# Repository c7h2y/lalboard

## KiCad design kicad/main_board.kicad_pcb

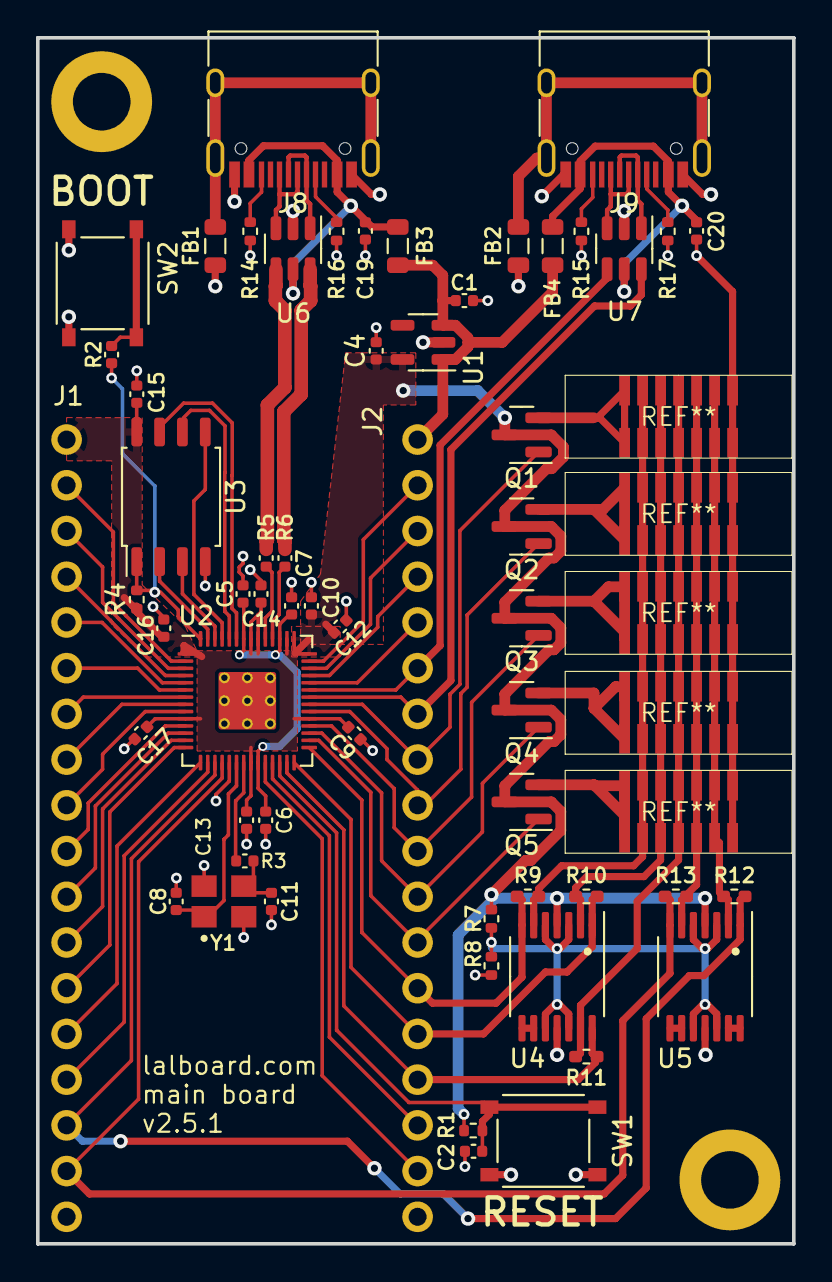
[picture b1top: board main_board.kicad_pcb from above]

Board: 2 copper layers, 42.0 x 67.0 mm, 60 parts (0 on the bottom side), 72 nets.

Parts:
C1: 10u; C_0402_1005Metric
C2, C5, C6, C9, C12, C13, C14, C15, C16, C17, C19, C20: 100n; C_0402_1005Metric
C4: 4.7u; C_0402_1005Metric
C7, C10: 1u; C_0402_1005Metric
C8, C11: 30pF; C_0402_1005Metric
FB1, FB2, FB3, FB4: CBG201209U500T; L_0805_2012Metric
H1, H2: MountingHole_Pad; MountingHole_3.2mm_M3_DIN965_Pad
J1, J2: Conn_01x18; PinHeader_1x18_P2.54mm_Vertical
J8, J9: TYPE-C-31-M-12; USB_C_Receptacle_HRO_TYPE-C-31-M-12
Q1, Q2, Q3, Q4, Q5: DMG2301L-7; SOT-23
R1: 1.5k; R_0402_1005Metric
R2, R3: 1k; C_0402_1005Metric
R4: 10k; R_0402_1005Metric
R5, R6: 27; C_0402_1005Metric
R7: 100k; R_0402_1005Metric
R8: 390k; R_0402_1005Metric
R9, R10, R11, R12, R13: 2k; R_0402_1005Metric_Pad0.72x0.64mm_HandSolder
R14, R15, R16, R17: 5.1k; R_0402_1005Metric
SW1: Reset; SW_TS-1187A-B-A-B
SW2: Boot; SW_TS-1187A-B-A-B
U1: XC6220B331MR; SOT-23-5
U2: RP2040; RP2040-QFN-56
U3: W25Q128JVS; SOIC-8_5.23x5.23mm_P1.27mm
U4, U5: COS724; TSSOP-14_4.4x5mm_P0.65mm
U6, U7: USBLC6-2SC6; SOT-23-6
Y1: Crystal_GND24; OSC_X322516MLB4SI

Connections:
+1V1: C5.1, C6.1, C7.1, U2.23 (DVDD), U2.45 (VREG_VOUT), U2.50 (DVDD)
+3.3V: C4.1, C9.1, C10.1, C12.1, C13.1, C14.1, C15.1, C16.1, C17.1, J1.1, Q1.3 (D), Q2.3 (D), Q3.3 (D), Q4.3 (D), Q5.3 (D), R1.1, R4.1, R7.1, U1.5 (VOUT), U2.1 (IOVDD), U2.10 (IOVDD), U2.22 (IOVDD), U2.33 (IOVDD), U2.42 (IOVDD), U2.43 (ADC_AVDD), U2.44 (VREG_IN), U2.48 (USB_VDD), U2.49 (IOVDD), U3.8 (VCC), U4.4 (V+), U5.4 (V+)
+5V: C1.1, FB3.1, FB4.1, J2.1, U1.1 (VIN), U1.3 (CE)
/AMP_REF: R7.2, R8.1, U4.3 (+), U4.5 (+), U4.10 (+), U4.12 (+), U5.3 (+), U5.5 (+), U5.10 (+), U5.12 (+)
/COL1: R9.2, U4.6 (-)
/COL1_AMP: J2.13, R9.1, U2.29 (GPIO18), U4.7
/COL2: R10.2, U4.2 (-)
/COL2_AMP: J2.14, R10.1, U2.28 (GPIO17), U4.1
/COL3: R11.2, U4.13 (-)
/COL3_AMP: J2.15, R11.1, U2.27 (GPIO16), U4.14
/COL4: R13.2, U5.6 (-)
/COL4_AMP: J1.17, R13.1, U2.18 (GPIO15), U5.7
/COL5: R12.2, U5.2 (-)
/COL5_AMP: J1.16, R12.1, U2.17 (GPIO14), U5.1
/D+: R5.1, U6.4 (I/O2)
/D-: R6.1, U6.6 (I/O1)
/GPIO0: J1.2, U2.2 (GPIO0)
/GPIO1: J1.3, U2.3 (GPIO1)
/GPIO2: J1.4, U2.4 (GPIO2)
/GPIO3: J1.5, U2.5 (GPIO3)
/GPIO4: J1.6, U2.6 (GPIO4)
/GPIO5: J1.7, U2.7 (GPIO5)
/GPIO6: J1.8, U2.8 (GPIO6)
/GPIO7: J1.9, U2.9 (GPIO7)
/GPIO8: J1.10, U2.11 (GPIO8)
/GPIO9: J1.11, U2.12 (GPIO9)
/GPIO10: J1.12, U2.13 (GPIO10)
/GPIO11: J1.13, U2.14 (GPIO11)
/GPIO12: J1.14, U2.15 (GPIO12)
/GPIO13: J1.15, U2.16 (GPIO13)
/GPIO26_ADC0: J2.5, U2.38 (GPIO26_ADC0)
/GPIO27_ADC1: J2.4, U2.39 (GPIO27_ADC1)
/GPIO28_ADC2: J2.3, U2.40 (GPIO28_ADC2)
/GPIO29_ADC3: J2.2, U2.41 (GPIO29_ADC3)
/QSPI_SCLK: U2.52 (QSPI_SCLK), U3.6 (CLK)
/QSPI_SD0: U2.53 (QSPI_SD0), U3.5 (DI(IO0))
/QSPI_SD1: U2.55 (QSPI_SD1), U3.2 (DO(IO1))
/QSPI_SD2: U2.54 (QSPI_SD2), U3.3 (IO2)
/QSPI_SD3: U2.51 (QSPI_SD3), U3.7 (IO3)
/QSPI_SS: R2.2, R4.2, U2.56 (QSPI_SS), U3.1 (~CS)
/RD+: J8.A6 (D+), J8.B6 (D+), U6.3 (I/O2)
/RD-: J8.A7 (D-), J8.B7 (D-), U6.1 (I/O1)
/ROW1: J2.12, Q5.1 (G), U2.30 (GPIO19)
/ROW2: J2.11, Q4.1 (G), U2.31 (GPIO20)
/ROW3: J2.10, Q3.1 (G), U2.32 (GPIO21)
/ROW4: J2.9, Q2.1 (G), U2.34 (GPIO22)
/ROW5: J2.8, Q1.1 (G), U2.35 (GPIO23)
/RUN: C2.2, R1.2, SW1.1, U2.26 (RUN)
/SWCLK: J2.17, U2.24 (SWCLK)
/SWD: J2.16, U2.25 (SWD)
/U1RX: J2.6, U2.37 (GPIO25), U7.4 (I/O2)
/U1RX_raw: J9.A6 (D+), J9.B6 (D+), U7.3 (I/O2)
/U1TX: J2.7, U2.36 (GPIO24), U7.6 (I/O1)
/U1TX_raw: J9.A7 (D-), J9.B7 (D-), U7.1 (I/O1)
/XIN: C8.1, U2.20 (XIN), Y1.1
/XOUT: R3.1, U2.21 (XOUT)
GND: C1.2, C2.1, C4.2, C5.2, C6.2, C7.2, C8.2, C9.2, C10.2, C11.2, C12.2, C13.2, C14.2, C15.2, C16.2, C17.2, C19.2, C20.2, FB1.2, FB2.2, H1.1, H2.1, J1.18, J2.18, J8.A1 (GND), J8.A12 (GND), J8.B1 (GND), J8.B12 (GND), J9.A1 (GND), J9.A12 (GND), J9.B1 (GND), J9.B12 (GND), R8.2, R14.2, R15.2, R16.2, R17.2, SW1.2, SW2.2, U1.2 (GND), U2.19 (TESTEN), U2.57 (GND), U3.4 (GND), U4.11 (V-), U5.11 (V-), U6.2 (GND), U7.2 (GND), Y1.2, Y1.4
unnamed: C11.1, R3.2, Y1.3
unnamed: J8.A5 (CC1), R16.1
unnamed: J8.B5 (CC2), R14.1
unnamed: FB1.1, J8.S1 (SHIELD)
unnamed: J9.A5 (CC1), R17.1
unnamed: J9.B5 (CC2), R15.1
unnamed: FB2.1, J9.S1 (SHIELD)
unnamed: R2.1, SW2.1
unnamed: R6.2, U2.46 (USB_DM)
unnamed: R5.2, U2.47 (USB_DP)
unnamed: U4.8, U4.9 (-)
unnamed: U5.8, U5.9 (-)
unnamed: U5.13 (-), U5.14
unnamed: C19.1, FB3.2, J8.A4 (VBUS), J8.A9 (VBUS), J8.B4 (VBUS), J8.B9 (VBUS), U6.5 (VBUS)
unnamed: C20.1, FB4.2, J9.A4 (VBUS), J9.A9 (VBUS), J9.B4 (VBUS), J9.B9 (VBUS), U7.5 (VBUS)

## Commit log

2025-07-13 refactor pcb file and add kicad footprint file
2025-07-13 add bom file
